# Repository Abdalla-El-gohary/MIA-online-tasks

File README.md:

# note
make a folder with name images and copy the test photos to it

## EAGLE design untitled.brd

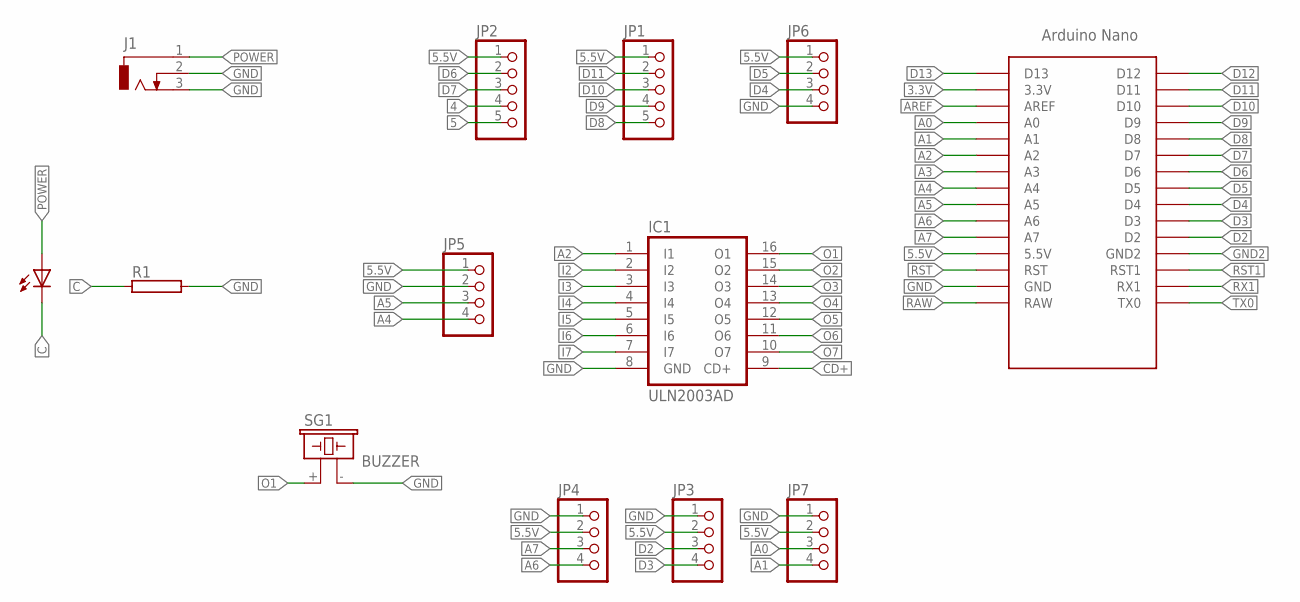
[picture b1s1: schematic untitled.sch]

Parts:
IC1: ULN2003AD; SO16
J1: CON_JACK; DCJ0303
JP1, JP2: PINHD-1X5; 1X05
JP3, JP4, JP5, JP6, JP7: PINHD-1X4; 1X04
R1: RMG100-H; TO-247-2H
SG1: BUZZER; F/CM12P
U$1: ARDUINO_NANO; NANO
U$2: LED5MM

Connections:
3.3V: U$1.3.3V
4: JP2.4
5: JP2.5
5.5V: JP1.1, JP2.1, JP3.2, JP4.2, JP5.1, JP6.1, JP7.2, U$1.5V (5.5V)
A0: JP7.3, U$1.A0
A1: JP7.4, U$1.A1
A2: IC1.1 (I1), U$1.A2
A3: U$1.A3
A4: JP5.4, U$1.A4
A5: JP5.3, U$1.A5
A6: JP4.4, U$1.A6
A7: JP4.3, U$1.A7
AREF: U$1.AREF
C: R1.1, U$2.K (C)
CD+: IC1.9 (CD+)
D2: JP3.3, U$1.D2
D3: JP3.4, U$1.D3
D4: JP6.3, U$1.D4
D5: JP6.2, U$1.D5
D6: JP2.2, U$1.D6
D7: JP2.3, U$1.D7
D8: JP1.5, U$1.D8
D9: JP1.4, U$1.D9
D10: JP1.3, U$1.D10
D11: JP1.2, U$1.D11
D12: U$1.D12
D13: U$1.D13
GND: IC1.8 (GND), J1.2, J1.3, JP3.1, JP4.1, JP5.2, JP6.4, JP7.1, R1.2, SG1.- (2), U$1.GND
GND2: U$1.GND1 (GND2)
I2: IC1.2 (I2)
I3: IC1.3 (I3)
I4: IC1.4 (I4)
I5: IC1.5 (I5)
I6: IC1.6 (I6)
I7: IC1.7 (I7)
O1: IC1.16 (O1), SG1.+ (1)
O2: IC1.15 (O2)
O3: IC1.14 (O3)
O4: IC1.13 (O4)
O5: IC1.12 (O5)
O6: IC1.11 (O6)
O7: IC1.10 (O7)
POWER: J1.1, U$2.A
RAW: U$1.RAW
RST: U$1.RST
RST1: U$1.RST1
RX1: U$1.RX1
TX0: U$1.TX0

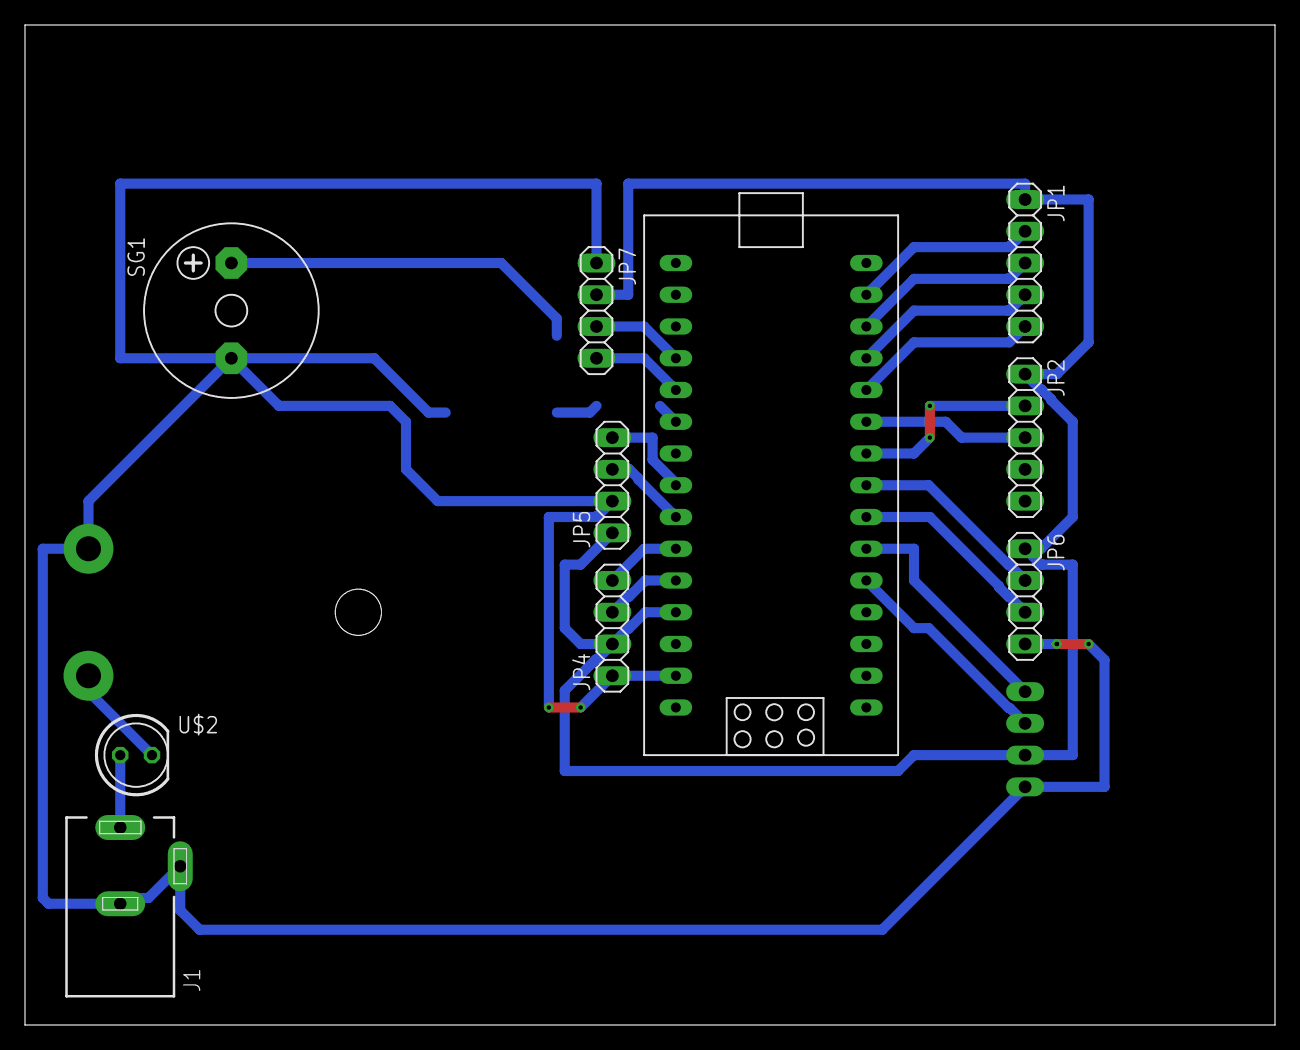
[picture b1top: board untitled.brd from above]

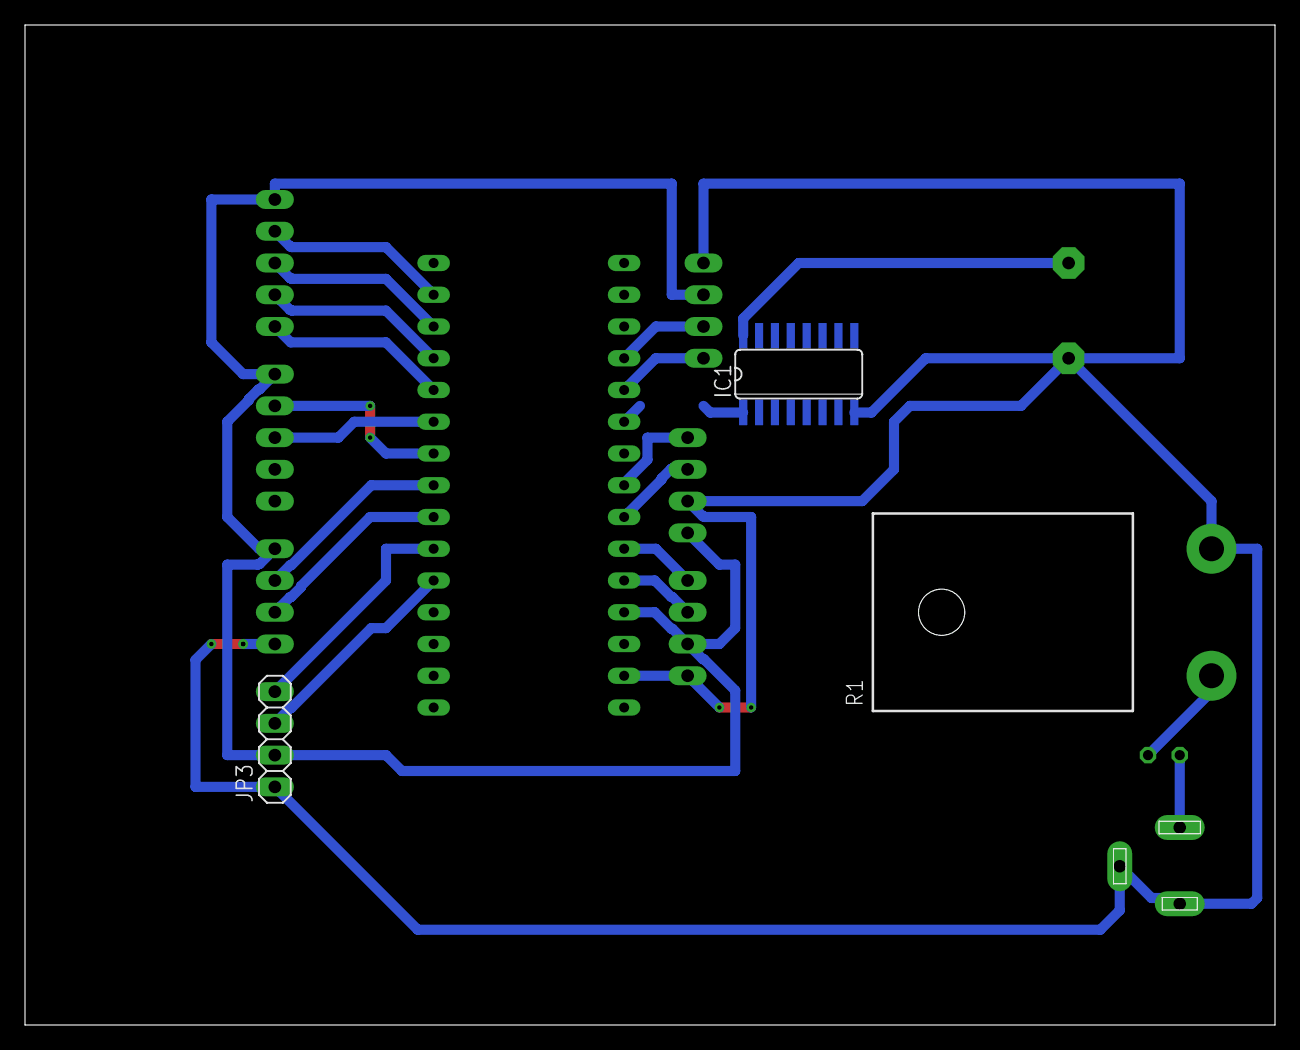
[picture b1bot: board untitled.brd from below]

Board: 2 copper layers, 100.0 x 80.0 mm, 13 parts (3 on the bottom side), 22 nets.

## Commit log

2022-08-10 Rename 1120.cbp to task3.cbp
2022-08-10 Rename 1120.depend to task3.depend
2022-08-10 Rename 1120.layout to task3.layout
